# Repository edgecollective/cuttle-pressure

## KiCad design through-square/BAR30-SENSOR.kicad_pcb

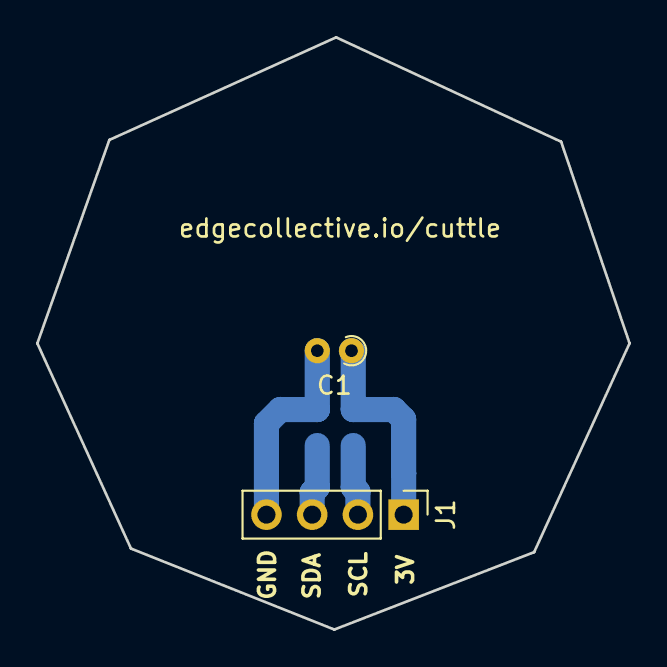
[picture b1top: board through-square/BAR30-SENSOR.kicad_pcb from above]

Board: 2 copper layers, 32.9 x 32.9 mm, 3 parts (0 on the bottom side), 4 nets.

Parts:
C1: 1uF; R_Axial_DIN0204_L3.6mm_D1.6mm_P1.90mm_Vertical
J1: Conn_01x04_Male; PinHeader_1x04_P2.54mm_Vertical
U2: MS583730BA; MS5837

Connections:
3V3: C1.1, J1.1, U2.2
GND: C1.2, J1.4, U2.1
SCL: J1.2, U2.3
SDA: J1.3, U2.4

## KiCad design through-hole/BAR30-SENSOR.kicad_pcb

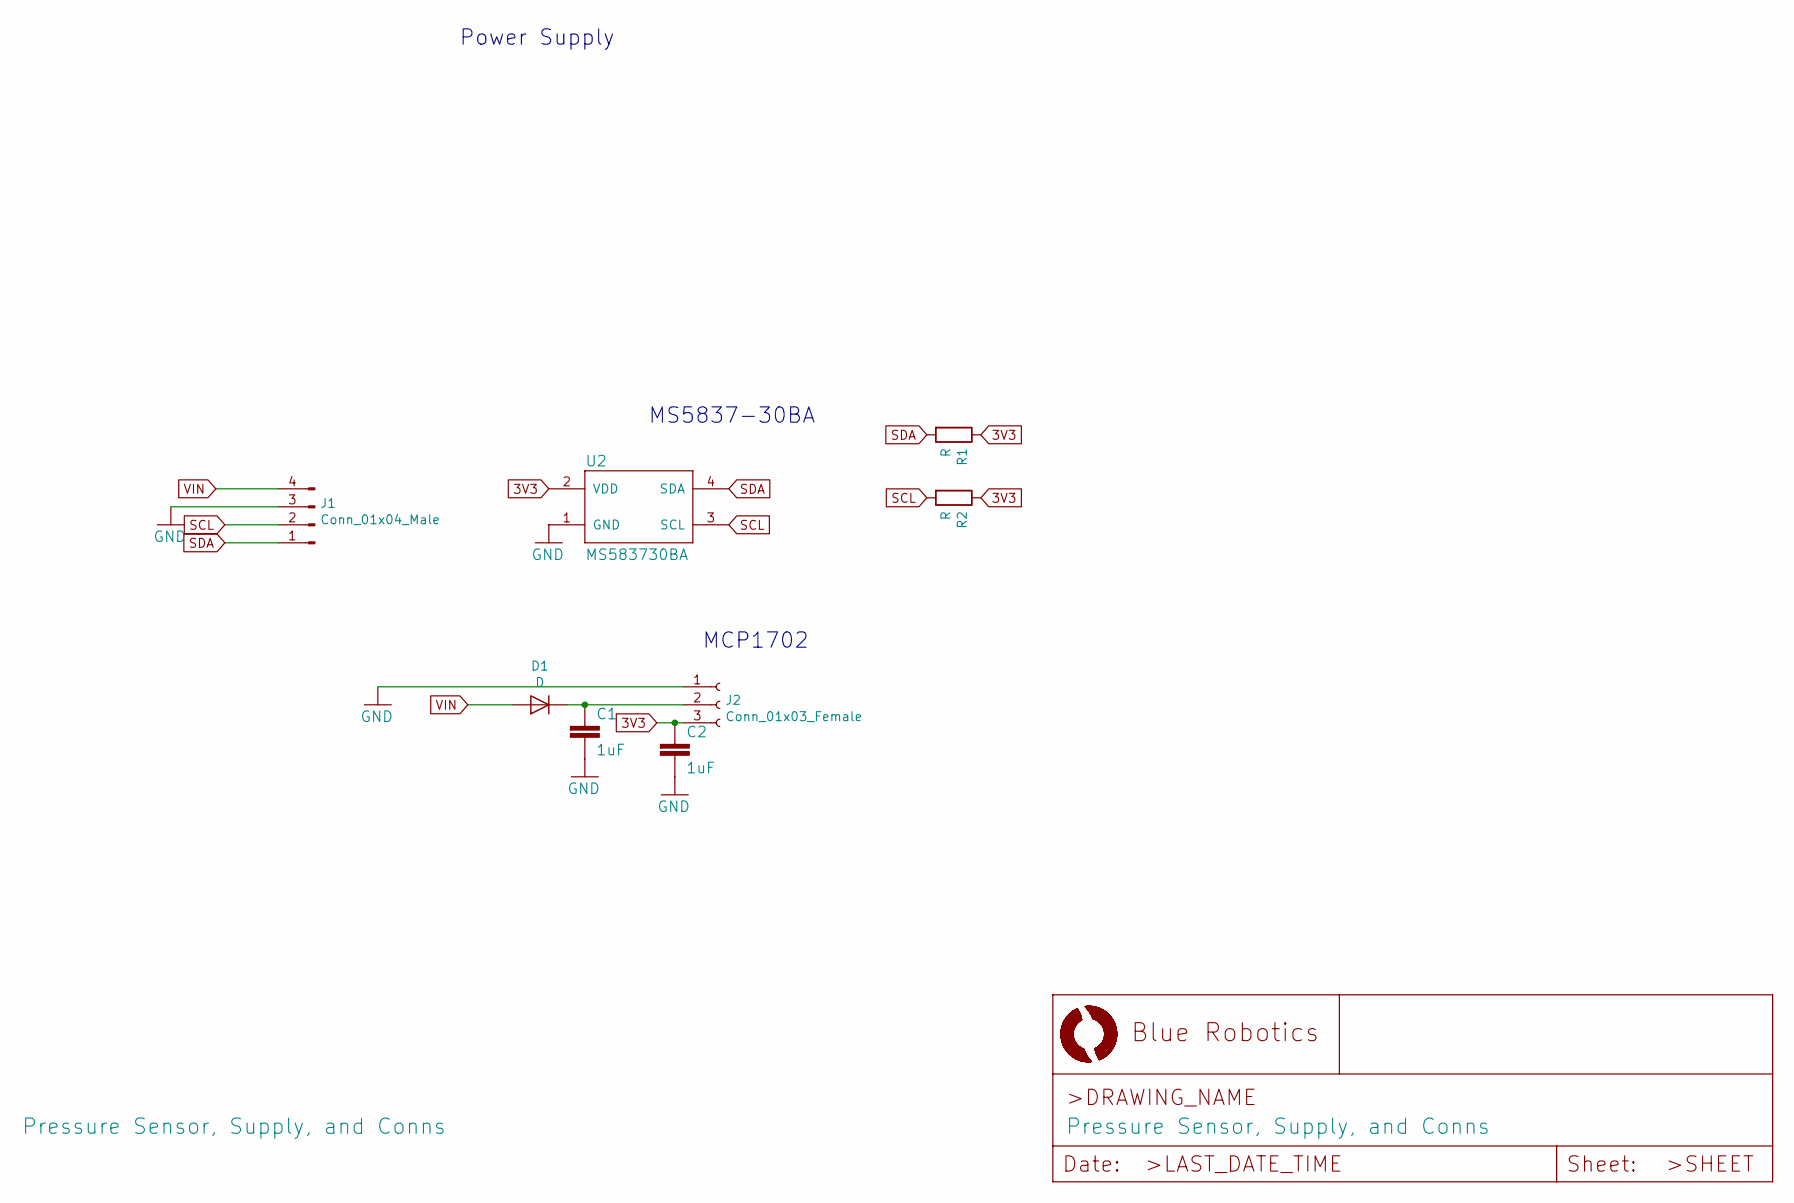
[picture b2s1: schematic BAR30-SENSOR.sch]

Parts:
C1, C2: 1uF; R_Axial_DIN0204_L3.6mm_D1.6mm_P2.54mm_Vertical
D1: D; D_DO-15_P5.08mm_Vertical_KathodeUp
J1: Conn_01x04_Male; PinHeader_1x04_P2.54mm_Vertical
J2: Conn_01x03_Female; PinSocket_1x03_P2.54mm_Vertical
R1, R2: R; R_Axial_DIN0204_L3.6mm_D1.6mm_P2.54mm_Vertical
U2: MS583730BA; MS5837

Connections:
3V3: C2.1, J2.3, R1.1, R2.1, U2.2 (VDD)
GND: C1.2, C2.2, J1.3, J2.1, U2.1 (GND)
unnamed: C1.1, D1.1 (K), J2.2
SCL: J1.2, R2.2, U2.3 (SCL)
SDA: J1.1, R1.2, U2.4 (SDA)
VIN: D1.2 (A), J1.4

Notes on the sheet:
MS5837-30BA
Power Supply
MCP1702

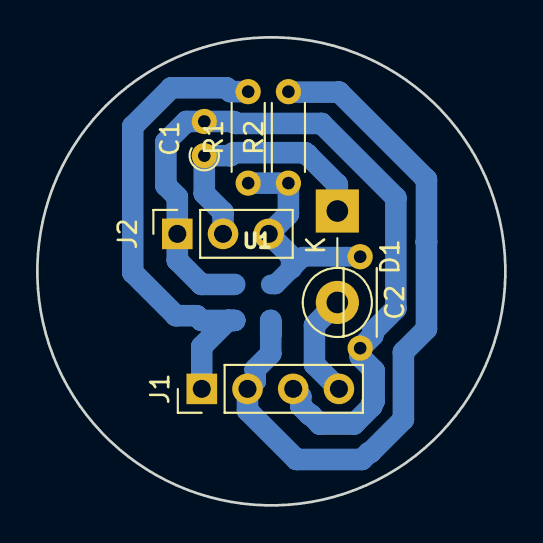
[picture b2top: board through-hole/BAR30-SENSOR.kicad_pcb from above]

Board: 2 copper layers, 26.0 x 26.0 mm, 8 parts (0 on the bottom side), 6 nets.

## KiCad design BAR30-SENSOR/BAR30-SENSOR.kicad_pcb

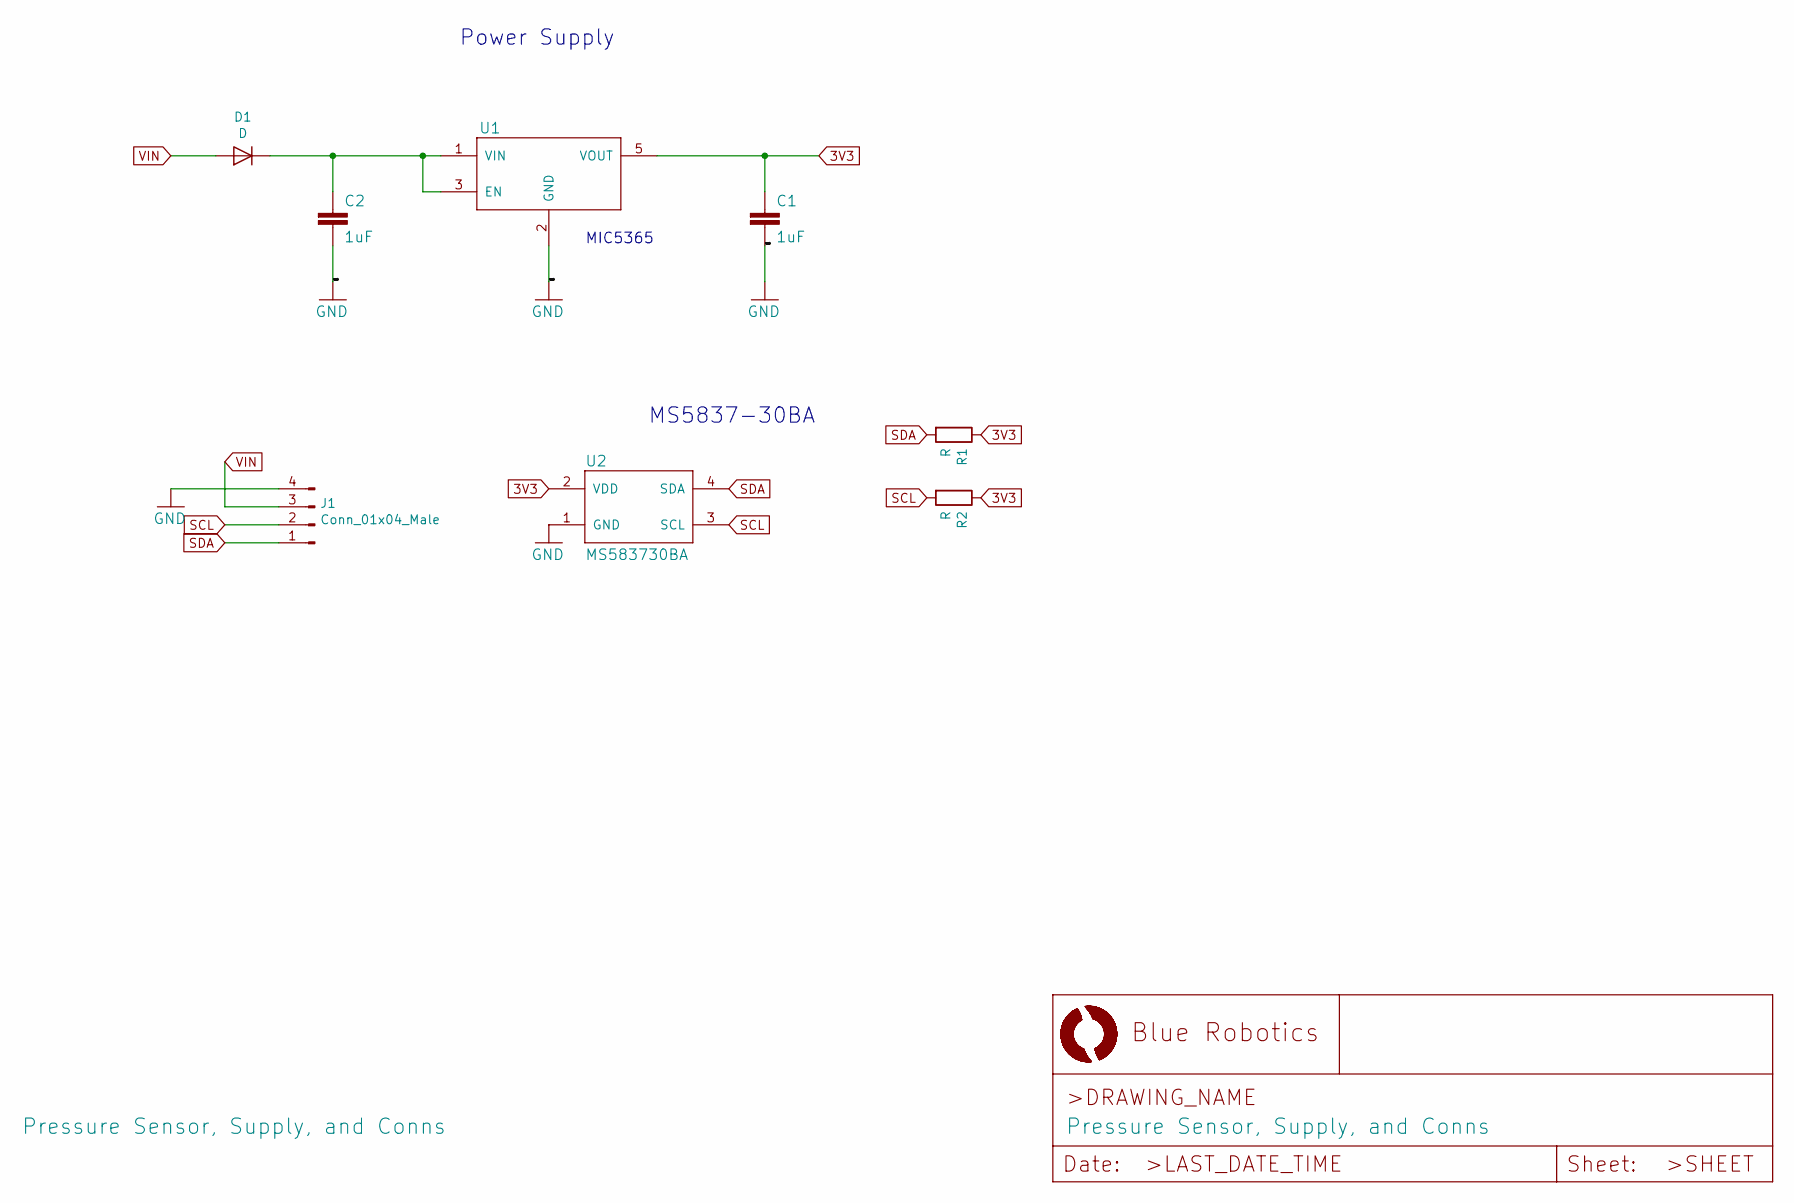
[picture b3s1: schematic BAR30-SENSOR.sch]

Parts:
C1, C2: 1uF; C_0603_1608Metric
D1: D; D_SOD-523
J1: Conn_01x04_Male; PinHeader_1x04_P2.54mm_Vertical
R1, R2: R; R_0603_1608Metric
U1: VREG-MIC5365; SC70-5L
U2: MS583730BA; MS5837

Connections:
3V3: C1.1, R1.1, R2.1, U1.5 (VOUT), U2.2 (VDD)
GND: C1.2, C2.2, J1.4, U1.2 (GND), U2.1 (GND)
unnamed: C2.1, D1.1 (K), U1.1 (VIN), U1.3 (EN)
SCL: J1.2, R2.2, U2.3 (SCL)
SDA: J1.1, R1.2, U2.4 (SDA)
VIN: D1.2 (A), J1.3

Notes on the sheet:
MS5837-30BA
Power Supply
MIC5365

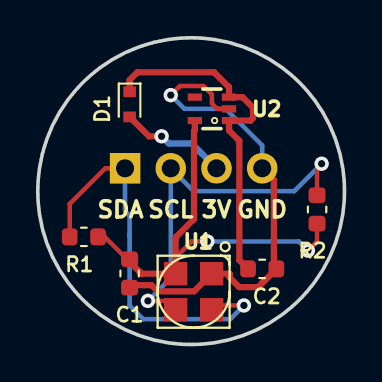
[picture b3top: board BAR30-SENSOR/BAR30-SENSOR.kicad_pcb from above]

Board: 2 copper layers, 17.0 x 17.0 mm, 8 parts (0 on the bottom side), 6 nets.
